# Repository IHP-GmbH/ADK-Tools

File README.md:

# adk-tools

Single Docker image for the heterogeneous integration flow: every tool of the
ecosystem, pre-wired, callable by name. Versions are pinned three ways: the
submodules under `tools/`, the staged sources and engines in `staging.pin`, and
the Nix inputs in `flake.lock`.

## Status

> [!WARNING]
> adk-tools is an alpha. What is checked is the build: `./build.sh` runs its
> verify gate on the image it makes. The flow's results are not: no assembly
> this image exports or checks is qualified, and the path that builds dies
> from RTL has not run end to end (`docs/E2E_BUILD_VARIANT.md`).

## Quickstart

A clone of this repository alone can neither build nor run anything today.
No image is published, to a registry or as a download: you build it locally
(see Build) and run the image you built. Building needs sources that are not
public yet.

### Build

Building needs Docker and Nix on the host, checkouts of the six sibling
repositories `staging.pin` lists at the commits it pins (beside this
repository, or in the directory `STAGE_SIBLINGS` names), and the `die-views/`
folder of an adk-examples checkout (not public yet) whose records match
`die-views.sha256` (`STAGE_DIE_VIEWS_DIR` names that folder). None of the six
pinned commits can be fetched from a public remote yet (`ci/pin-set.json` marks
them `"reachable": "local-only"`). The two `--check` calls below find a missing
piece in seconds; run them first.

`build.sh` compiles the pinned toolchain into one Docker image and copies
OpenROAD, LibreLane, its interpreter, the sg13g2 PDK and the simulation
engines and viewers from the host's Nix store into the image's own store (see
Notes). At the commit you build, realise them once before the build and keep
the result links (they keep the paths from garbage collection). Most come from
the binary cache; vams-devshell and Xschem build locally, and mixsim-iverilog
builds locally and runs Icarus Verilog's regression suite.

```bash
# the clone lives at ADK_TOOLS_ROOT, outside ADK_WORK (see below); the
# die-views/ folder of the adk-examples checkout at ADK_EXAMPLES_ROOT has to
# match die-views.sha256
export ADK_TOOLS_ROOT=~/adk-tools ADK_EXAMPLES_ROOT=~/adk-examples
export STAGE_DIE_VIEWS_DIR="$ADK_EXAMPLES_ROOT/die-views"
git clone --branch vYYYY.MM --recurse-submodules https://github.com/IHP-GmbH/ADK-Tools.git \
    "$ADK_TOOLS_ROOT"
cd "$ADK_TOOLS_ROOT"
./stage-sources.sh --check && ./stage-die-views.sh --check
nix build .#openroad .#librelane .#librelane-python .#sg13g2-pdk \
    .#cosim-devshell .#mixsim-ngspice .#mixsim-iverilog .#sg13g2-osdi \
    .#gtkwave .#gaw .#xschem .#vams-devshell
# ~1 h the first time, cached afterwards; JOBS=N overrides the default 8
# parallel compile jobs
./build.sh

# run.sh takes the image by its ID (sha256:<64 hex>), never a tag, and has no
# default: read the ID of the image you just built once
export ADK_TOOLS_IMAGE="$(docker image inspect --format '{{.Id}}' adk-tools:dev)"
"$ADK_TOOLS_ROOT/run.sh" --examples "$ADK_EXAMPLES_ROOT"
```

The examples' `release-lock.json` names the reference image they were checked
on and the pin set it was built from. Your build has its own ID: `run.sh`
names both IDs in one note line and runs it, and refuses an image whose
`org.ihp.adk-tools.pin-set` label, which `build.sh` writes, is not the lock's
pin set.

### Running it

With `ADK_TOOLS_IMAGE` set:

```bash
# X11 passthrough for the GUIs; ~/adk-work mounted at /work; capped at 8g and
# 4 CPUs, change with ADK_MEM_LIMIT and ADK_CPUS; ADK_NETWORK=none runs it
# with no network
./run.sh                              # interactive shell
./run.sh --examples ~/adk-examples    # the examples, from an adk-examples checkout,
                                      # held to its lock (an image
                                      # without the closure label needs the
                                      # host's Nix store, see Notes)
./run.sh bash < script.sh             # run a script piped in, no terminal needed
```

Inside the shell, `adk-tools` prints this table with the pinned versions of
the running image.

The examples live in their own repository, adk-examples, which is not public
yet. Its `release-lock.json` names the reference image they were checked on
and its pin set, and `run.sh --examples <checkout>` starts an image of that pin
set, with the checkout mounted read-only at `/examples`. Each example's
`README.md` is its page: what to run, and what the run should show.
`examples/two_die_interposer` in this repository is not one of them: it is the
test fixture of the image's own checks.

## Working in the shared folder

`run.sh` mounts a host directory (`~/adk-work`, override with `ADK_WORK=...`) at
`/work` inside the container, so files written on either side are immediately
visible on the other. A relative `ADK_WORK` is taken from the directory you call
`run.sh` from; either way `run.sh` binds it by its absolute path and names it on
its first stderr line, `run.sh: /work is <path>`. What a program calling
`run.sh` can rely on (its notes, exit codes and refusals) is in
[docs/RUN_SH.md](docs/RUN_SH.md).

Keep the adk-tools clone apart from that directory: clone it once to
`ADK_TOOLS_ROOT` (`~/adk-tools` above), outside `ADK_WORK`, leave it at the
version of the image you run (the release tag, or the commit you built), and
call `run.sh` by its path from wherever you work. `run.sh` refuses to start when `ADK_WORK` holds its clone, which the
container would then see and could write, or lies inside it, where a git clean
in the clone would delete your runs.

```bash
export ADK_TOOLS_ROOT=~/adk-tools ADK_WORK=~/adk-work ADK_EXAMPLES_ROOT=~/adk-examples
"$ADK_TOOLS_ROOT/run.sh" --examples "$ADK_EXAMPLES_ROOT"
```

The work directory is the recommended place to keep your designs: edit
with the bundled GUIs/editors in the container, keep the files (and your git
history) on the host. The image writes nothing there unless you ask; two
subdirs are the usual layout:

```
/work/<example>            an example copied in from /examples, as its page says
/work/heterogenic-designs  your persistent designs (survives image rebuilds)
```

The runtime image carries no examples. Start it with an adk-examples checkout
(`run.sh --examples`); inside the container, `adk-example` prints that line.

Scaffold a new design instead of starting from a blank dir:

```bash
adk-new-project my_design          # -> /work/heterogenic-designs/my_design
```

It lays out the same structure as the bundled example, a clean split between
source and generated artifacts:

```
my_design/
  kicad/       KiCad source you author (schematic, PCB, .pretty, fp-lib-table)
  chiplets/    die GDS inputs (+ pin lists) for the gds-to-kicad prior steps
  outputs/     export products: <board>.chiplet + MANIFEST.md at the root; the
               GDS layouts + DRC sidecars under outputs/layout/; the DRC
               reports under outputs/reports/
```

Author the board under `kicad/`, run the Chiplet Export plugin in pcbnew with
its output directory set to the sibling `outputs/`, then open the result with
`chiplet-studio outputs/<board>.chiplet`. The scaffolded `.gitignore` already
keeps the heavy/scratch files (the full `_complete.gds`, the intermediate
`.hyp`, the DRC working dir, logs and KiCad caches) out of git while tracking
the light deliverables, so `git init` in the project is ready to use.

## Tools

| Command          | Tool                                  | Kind |
|------------------|---------------------------------------|------|
| `kicad`          | KiCad fork (+ `pcbnew`, `kicad-cli`, chiplet export plugin preloaded) | GUI |
| `chiplet-studio` | 3D assembly viewer / `.chiplet` editor | GUI |
| `gds-to-kicad`   | GDS -> KiCad symbol + footprint generator (unified GUI) | GUI |
| `hyp-to-gds`     | HyperLynx -> GDS converter             | CLI |
| `adk-drc`        | ADK assembly DRC runner                | CLI |
| `klayout`        | KLayout (version pinned by the studio submodule) | GUI/CLI |
| `adk-smoke`      | Board export + dual DRC, asserts green  | CLI |

Data roots baked in (and exported as env), named after their IHP
repositories: `INTERPOSER_PDK_ROOT=/opt/adk-tools/OpenIntM4TM2`,
`INTERCONNECT_PDK_ROOT=/opt/adk-tools/IHP-Interconnect-IntM4TM2`,
`PDK_ROOT=/opt/adk-tools/IHP-Open-PDK` (SG13G2 KLayout slice: the
SG13_dev PCell library + tech, pinned in the Dockerfile, so
`hyp-to-gds` builds vias from real `via_stack` PCells, not the
rectangle fallback), plus `ADK_ROOT` and `GDS_TO_KICAD_ROOT`. The
two-die interposer test fixture lives in this repo under `examples/` (not in the
runtime image; the verify build puts it at `/opt/adk-tools/examples`,
regenerates it and DRC-gates it); it follows the same `kicad/` + `chiplets/` + `outputs/` template
as a scaffolded project. Python worker venv: `/opt/adk-tools/venv`
(`KICAD_CHIPLET_PYTHON` already points at it).

Dies on an IntM4TM2 interposer mount on the plane the interposer PDK states,
`beol.attachment_surface_z_um` in `libs.tech/intm4tm2_stack.json`.
`ci/check_attach_plane.py` holds every IntM4TM2 `.chiplet` in the plugin, in
Studio and in `examples/` to it, and the consumers' copies of the PDK's stack
files to the PDK; it runs in CI and in every verify build, and its docstring
states exactly which files it walks.
`ci/check_kicad_templates.py` does the same for the staged interposer-pnr and
packaging-flow copies of the PDK's KiCad rule templates, in every verify build.

`openroad/` holds a host-side sidecar that lints an assembly with OpenROAD's
`read_3dbx` / `check_3dblox`, using a separately pinned OpenROAD image. It is
not part of the distribution image; see `openroad/README.md`, which also
states plainly what that linter does and does not catch.

The interposer KLayout technology is pre-registered (`KLAYOUT_PATH`
includes the OpenIntM4TM2 tree), so exported interposer/assembly GDS
files open with named, colored layers: `klayout -n intm4tm2 <file>.gds`,
or pick `intm4tm2` in the technology selector.

The PDK's `IntM4TM2 Interposer > Verification` menu (`Interposer DRC…`,
`Interposer LVS…`) needs a KLayout with Qt bindings, and the image's KLayout
is built without them: the entries are listed, and choosing one reports
`AttributeError: module 'pya' has no attribute 'QDialog'`. KLayout itself
starts normally, and the PDK's other menu entries do not use Qt bindings. The
runners behind that menu are
unaffected; call them directly from `libs.tech/klayout/tech/drc/run_drc.py`
and `libs.tech/klayout/tech/lvs/run_lvs.py` under `$INTERPOSER_PDK_ROOT`.

## Updating an existing clone

This section and the two after it are for building (Quickstart, Build). To run
a newer release, check out its tag and build it.

```bash
# the Quickstart's exports, again in a fresh shell
export ADK_TOOLS_ROOT=~/adk-tools ADK_EXAMPLES_ROOT=~/adk-examples
export STAGE_DIE_VIEWS_DIR="$ADK_EXAMPLES_ROOT/die-views"
cd "$ADK_TOOLS_ROOT"
git fetch --tags
git checkout vYYYY.MM    # a release clone sits on a tag, so there is nothing to pull
git submodule update --init --recursive
./stage-sources.sh --check && ./stage-die-views.sh --check
./build.sh    # cached stages rebuild only what changed
```

The sibling checkouts have to hold the new pins (a `git fetch` in each), and
the adk-examples checkout has to hold die-views records that match the new
`die-views.sha256` (update it until they do); the two `--check` calls say
which one does not.

One-time cleanups, depending on how old the clone is:

- Clones from before the demo moved into `examples/` still carry the
  removed `kicad_designs` submodule as leftovers:
  `rm -rf tools/kicad_designs .git/modules/tools/kicad_designs`
- If the default job count changed since your last build (it keys the
  compile layers), the heavy stages rebuild once (~40 min), then cache
  normally again.
- A `/work/example` from an older image stays as it is. It was the demo copied
  from this clone; the examples now come from adk-examples.

## Branch model

`main` is frozen per release and pins each tool's `main`. `dev` is where the
suite is integrated and tested, and pins each tool's `dev` branch instead, so
`git submodule update --remote` follows the right side on each branch. Tools
without ongoing work keep `branch = main` in `.gitmodules` on both sides until
they need a `dev`; check that file for which is which.

Feature work happens on a branch of the tool's `dev`, and is evaluated by
checking it out in the submodule and rebuilding (see below). A release folds
each tool's `dev` into its `main`, then re-pins adk-tools `main`.

## Updating / testing a tool release

```bash
# bump one tool to its latest upstream branch (dev on this branch, main on main)
git submodule update --remote tools/adk
git add tools/adk
python3 -B ci/pin_set.py    # the pin set records every staged gitlink
git commit -am "Bump adk to <ref>"
./build.sh

# try an arbitrary branch of one tool against the rest of the pinned stack
cd tools/chiplet-studio && git fetch && git checkout feature/x && cd ../..
./build.sh
```

The pin set takes each tool's commit from the gitlink git has staged, not from
the submodule's checkout, so stage the bump before you regenerate it. The
image is labelled with the committed pin set: `build.sh` refuses a
`ci/pin-set.json` that differs from the commit or from what the staged pins
give, so commit the regenerated file before you build. In the second case
nothing is staged: the image carries `feature/x` while its
`org.ihp.adk-tools.pin-set` label still names the pinned commit, so do not run
such an image under an examples checkout's `release-lock.json`.

`build.sh` always builds the `verify` stage first: it regenerates the
two-die interposer demo headless through the full pipeline (pcbnew -> writers ->
hyp_to_gds -> assembly DRC), runs the Chiplet Studio test suite and the
plugin test suite inside the image. A broken combination does not produce a
tagged image. `--skip-verify` exists for quick iteration only.

To develop a Python tool against the pinned stack, mount your checkout over
the baked-in copy:

```bash
docker run --rm -it -v "$PWD/chiplet_kicad_plugin":/opt/adk-tools/chiplet_kicad_plugin ... adk-tools:dev
```

## Notes

- The image's Magic is 8.3.610, from LibreLane's Nix closure, and the PDK's Magic
  techfiles require 8.3.617 (ihp-sg13g2) and 8.3.657 (ihp-sg13cmos5l), so a LibreLane
  Classic flow run in the image fails at `Magic.StreamOut`. Build dies with
  chiplet-flow's Chiplet flow (`meta.flow: Chiplet`), which runs no Magic step.
- The image carries OpenROAD, LibreLane, its interpreter, the sg13g2 PDK and
  the LibreLane launcher in its own `/nix/store`: the closure
  `nix/host-closure.txt` lists, each path pinned with its narHash in
  `nix/host-closure.lock`. `build.sh` refuses to pack unless every path is in
  the build host's store with that narHash, and the verify stage recomputes
  each one in the image. The image sets `OPENROAD`, `ADK_NIX_LIBRELANE`,
  `ADK_NIX_LIBRELANE_PYTHON`, `ADK_NIX_SG13G2_PDK` and the launcher pair in its
  ENV, and carries the `org.ihp.adk-tools.nix-closure-inside` label (the lock's
  sha256). For such an image `run.sh` mounts nothing of the host's store, passes
  none of those variables, ignores `ADK_OPENROAD` with a note, and needs no Nix
  on the host. It refuses an image whose label is there but is not a sha256.
- An image without that label needs the host's
  Nix store: `run.sh` takes, read-only, the OpenROAD the image's
  `org.ihp.adk-tools.nix-openroad` label names (staging.pin's
  `NIX_OPENROAD_OUTPATH`), or `ADK_OPENROAD` when set, and sets `OPENROAD` to
  it. It refuses to start when the host has no Nix store or that path is not in
  it, with a line starting `needs Nix on the host:`; realise it with
  `nix build .#openroad`. An image without the `nix-openroad` label needs
  `ADK_OPENROAD`.
- What goes in from the host's store, for such an image, is the closure of OpenROAD, LibreLane,
  its interpreter and the sg13g2 PDK, listed in `nix/host-closure.txt`.
  `build.sh` refuses unless that file is the store's closure of the four, and
  writes it on the image as the `org.ihp.adk-tools.nix-host-closure` label (the
  paths joined by single spaces) with its sha256 in
  `org.ihp.adk-tools.nix-host-closure-sha256`. `run.sh` checks the list against
  its sha256 and binds each listed path on its own, read-only, at its own path,
  so the image's own `/nix/store` stays visible beside them; a listed path the
  host lacks is not bound and is counted in a note. No launch calls Nix. An
  image without the two labels, or an `ADK_OPENROAD` the list does not name,
  gets the whole host store instead, which hides the image's own store paths.
  A die run recorded under another sg13g2-pdk path names a PDK outside the
  list; rebuild that die under this image's PDK.
- Such an image ships no LibreLane, no LibreLane interpreter and no sg13g2 PDK
  either; a page that builds a die in the container takes them from the same
  store. `run.sh` passes the paths the image's `org.ihp.adk-tools.nix-librelane`,
  `org.ihp.adk-tools.nix-librelane-python` and `org.ihp.adk-tools.nix-sg13g2-pdk`
  labels name (staging.pin's `NIX_LIBRELANE_OUTPATH`, the `bin/python3.<minor>`
  of `NIX_LIBRELANE_PYTHON_OUTPATH`, and `NIX_SG13G2_PDK_OUTPATH`) as
  `ADK_NIX_LIBRELANE`, `ADK_NIX_LIBRELANE_PYTHON` and `ADK_NIX_SG13G2_PDK`, the
  names the Nix build shell sets, when they are on the host and in the list
  bound. When one is not, it says so and starts anyway, and that page refuses;
  realise them with
  `nix build .#librelane .#librelane-python .#sg13g2-pdk`.
- The image does carry the co-simulation engine chiplet-cosim runs: Icarus and
  a python3.13 with cocotb 2.0.0 in its own site-packages, at the Nix store
  paths staging.pin's `NIX_COSIM_*` lines name, under the image's `/nix/store`.
  `COSIM_DEVSHELL` links to the flake's `cosim-devshell`, a store path whose
  `bin/` holds only `python3`, `iverilog` and `vvp`, linked into them; none is
  on `PATH`. Only when `run.sh` mounts the whole host store (see above) does
  that hide the image's; then the engine comes from the host's store, and
  `run.sh` says when it is not there; realise it with
  `nix build .#cosim-devshell`.
- It carries a mixed-signal engine the same way: ngspice 45, an Icarus with
  libvvp, and the six sg13g2 OSDI models compiled for generic x86-64, at the
  paths staging.pin's `NIX_MIXSIM_*` and `NIX_SG13G2_OSDI_OUTPATH` lines name.
  `MIXSIM_DEVSHELL` holds `bin/ngspice`, `bin/iverilog`, `bin/vvp`,
  `lib/libvvp.so`, `lib/ngspice` (with the ivlng shim d_cosim loads) and
  `osdi/`; none is on `PATH`. Give d_cosim `lib/libvvp.so` and
  `lib/ngspice/ivlng` by absolute path, and load the models with `pre_osdi`.
  Under a whole-store mount, realise it with
  `nix build .#mixsim-ngspice .#mixsim-iverilog .#sg13g2-osdi`.
- For a gf180mcuD die in a mixed case it carries that PDK's `design.ngspice`
  and `sm141064.ngspice` and no cell library, at the GF180 layer sheet's
  commit. `COSIM_GF180_ROOT` points at them, and it is the only place
  chiplet-cosim reads a gf180mcuD models entry's root from.
- For a transistor-level ihp-sg13g2 die it carries, under
  `$PDK_ROOT/ihp-sg13g2`, every ngspice model file the MOS, diode, resistor
  and capacitor corner libraries include, in any section and at any depth, and
  the stdcell spice (`sg13g2-models.sha256` lists them, and
  `ci/check_sg13g2_models.py` recomputes that list), at the slice's commit, and
  copies of the OSDI files `psp103`, `psp103_nqs`, `r3_cmc` and `mosvar` in
  `libs.tech/ngspice/osdi`. A link would not do there: chiplet-cosim refuses
  an OSDI file that resolves outside the PDK.
- It carries two waveform viewers and a schematic editor the same way, and
  these are on `PATH`: `gtkwave` (GTKWave 3.3.121, for VCD and FST), `gaw`
  (GAW, for ngspice's raw files, binary or ASCII) and `xschem` (Xschem
  3.4.8RC, upstream commit 8d2088e, with its device symbols under
  `XSCHEM_SHAREDIR`), at the paths staging.pin's `NIX_GTKWAVE_OUTPATH`,
  `NIX_GAW_OUTPATH` and `NIX_XSCHEM_OUTPATH` name. All three need a display
  (`ADK_DISPLAY`); `xschem -x -q -n -s` netlists without one. Under a
  whole-store mount, realise them with `nix build .#gtkwave .#gaw .#xschem`.
- It carries a Verilog-AMS engine the same way: gnucap and its Verilog-AMS
  model compiler in one prefix, at the paths staging.pin's
  `NIX_VAMS_GNUCAP_OUTPATH` and `NIX_VAMS_DEVSHELL_OUTPATH` name.
  `VAMS_DEVSHELL` holds `bin/gnucap`, `bin/gnucap-conf`, `bin/gnucap-mg-vams`,
  `bin/gnucap-modelgen`, `bin/g++` and `bin/c++`; none is on `PATH`. Compile a
  model with `gnucap-mg-vams` and that `g++` (flags from
  `gnucap-conf --cppflags`), then `load` the `.so` in gnucap. Under a
  whole-store mount, realise it with `nix build .#vams-devshell`; it is not
  in the binary cache, so that builds it.
- It carries the EDA views of the two built bondpad dies, their gate-level
  netlists and CDL among them, under `ADK_DIE_VIEWS`
  (`/opt/adk-tools/die-views`), one directory per die named by the layout
  sha256 its contract binds. A die with no directory there has no
  views. Copy a record out before using it; the image's copy is the reference.
  `die-views.sha256` pins every byte, and `staging.pin` pins that listing as
  `STAGE_DIE_VIEWS_SHA256`. Building the image needs the records:
  set `STAGE_DIE_VIEWS_DIR` to the directory holding their `records/`.
- GUIs need an X server. `run.sh` takes the display from `ADK_DISPLAY` (`:N`,
  or `none`), else a local `DISPLAY`, else the newest ThinLinc session whose
  socket is yours, and passes its cookie from `XAUTHORITY`, the ThinLinc
  session or `~/.Xauthority`, whichever holds one for that display. It prints
  the display it chose. The image itself forces Mesa's
  software path (`LIBGL_ALWAYS_SOFTWARE=1`, `GALLIUM_DRIVER=llvmpipe`, set in
  the Dockerfile) so the GUIs stay stable over remote X without a GPU;
  otherwise KiCad's GL canvas crashes when the host can't provide a DRI3
  device. Pass a real GPU and `-e LIBGL_ALWAYS_SOFTWARE=0` for hardware
  acceleration.
- The image bundles GPL-licensed tools: the pinned submodules under `tools/`,
  public in the IHP-GmbH org; the staged trees `staging.pin` pins, not public
  yet, whose source the image carries as git checkouts under
  `/opt/adk-tools/staging/<tree>`; and programs from the Nix closures copied
  into the image (Icarus Verilog, GTKWave, GAW, Xschem, gnucap and
  modelgen-verilog, nix-eda's KLayout, and the OpenSTA inside OpenROAD), whose
  source is at the revisions `flake.lock` and `flake.nix` pin. `NOTICE.md`
  lists them all.
- KiCad ships the official v9 symbol/footprint libraries (pinned tag,
  `KICAD_LIBS_TAG` build arg). 3D model packages are not included.
- Text editors are bundled for in-container edits to files under `/work`:
  `vim` (terminal) and `featherpad` (a light Qt GUI editor; needs X, like the
  other GUIs).

## License & notices

This repository is **GPL-3.0-or-later** (`LICENSE`), with one rule on top: a
file's own `SPDX-License-Identifier` line decides its license. The record format
schemas in [`formats/`](formats/) and the files of ours whose SPDX line says
Apache-2.0 (most of `ci/`, `nix/`, `nix-tail/`, their tests and `flake.nix`) are
**Apache-2.0**; its text is in
[`formats/LICENSE`](formats/LICENSE). A file with no SPDX line is under `LICENSE`,
and the third-party files `NOTICE.md` lists keep their own license.
The image is a **mere aggregation** of independently licensed tools; each keeps its
own license, and the bundled set spans GPL, Apache-2.0, CC-BY-SA-4.0 and permissive
(MIT/BSD) licenses. See
[`NOTICE.md`](NOTICE.md) for the per-component licenses, source URLs, and the GPL
corresponding-source obligation that applies when you redistribute the image.

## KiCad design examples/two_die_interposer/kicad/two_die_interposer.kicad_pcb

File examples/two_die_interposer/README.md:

# two_die_interposer

This folder is the test fixture of the image's own checks (the gds2kicad prior
steps, the writers, adk-smoke, carrier DRC, the reproducibility check). It is
not an example for users: those live in the adk-examples repository, and
`run.sh --examples` mounts them.

Reference heterogeneous-design project for the adk-tools flow: two dies mounted
on an IntM4TM2 interposer, connected through cu-pillar / micro-bump interconnect
(2.5D), with wire-bond I/O pads at the interposer edge. It doubles as the
template that `adk-new-project` scaffolds, so its layout is the recommended one
for any new design.

## Layout

```
two_die_interposer/
  kicad/       KiCad source (the human-authored input)
    two_die_interposer.kicad_pro / .kicad_sch / .kicad_pcb
    two_die_interposer.kicad_sym    (project symbols, produced by gds2kicad)
    two_die_interposer.pretty/      (project footprints, produced by gds2kicad)
    sym-lib-table / fp-lib-table    (register those two libraries with the project)
  chiplets/    gds2kicad prior-steps inputs (see chiplets/README.md)
    Metal_Test.gds                 die layout shared by both dies
    metal_test_chiplet.pins.json   curated 58-pad pin list
  outputs/     export products written by the Chiplet Export plugin
    two_die_interposer.chiplet            chiplet-studio entry point
    MANIFEST.md                           index of the products
    layout/    GDS layouts + their sidecars
      two_die_interposer_interposer.gds   referenced by the .chiplet
      *.boundaries.json / *.ixn_methods.json  assembly-DRC sidecars
    reports/   DRC reports: *_assembly_drc.lyrdb, *_cupillar_drc.json
    (regenerated, git-ignored: layout/_complete.gds, .hyp, reports/assembly_drc/, logs/)
```

The `.chiplet` references its interposer GDS by a `layout/<file>` relative path,
which chiplet-studio resolves against the `.chiplet`'s own directory; it then
auto-detects the `_complete.gds` from that same `layout/` dir, and the assembly
DRC finds each `*.boundaries.json` next to its GDS. So the GDS layouts and their
sidecars travel together under `layout/`, the DRC reports under `reports/`, and
only the `.chiplet` + `MANIFEST.md` sit at the `outputs/` root. Each die's own
layout is `chiplets/Metal_Test.gds`, shipped with the example: the footprint (and
the `.chiplet` it produces) reference it board-relative as
`../chiplets/Metal_Test.gds`, so the export and chiplet-studio resolve the die
layout from the example itself, not from any external tool tree. This is the same
die that seeds the reproducible prior steps below.

## Prior steps: chiplet footprints and symbols (gds2kicad)

The KiCad library this board is built on (`kicad/two_die_interposer.pretty/*` and
`kicad/two_die_interposer.kicad_sym`) is produced from the chiplet layouts with
the gds2kicad tools, before any board work starts. Those inputs and the exact
recipe live in `chiplets/` (see `chiplets/README.md`). The verify build reruns
the reproducible steps and gates them: the die symbol and the I/O pad are
regenerated and diffed against the committed library, the pin list is checked
against the committed footprint, and the footprint converter is run on
`Metal_Test.gds` as a liveness check.

## Open it

The runtime image does not carry this project. Copy it on the host from the
adk-tools clone you run `run.sh` from, into the folder mounted at `/work`
(`/work/example` is the disposable spot; for persistent work use your own area):

```bash
cp -r "$ADK_TOOLS_ROOT/examples/two_die_interposer" "$ADK_WORK/example"
mkdir -p "$ADK_WORK/heterogenic-designs"
cp -r "$ADK_TOOLS_ROOT/examples/two_die_interposer" "$ADK_WORK/heterogenic-designs/"
```

Then open the copy:

```bash
chiplet-studio /work/example/outputs/two_die_interposer.chiplet
kicad          /work/example/kicad/two_die_interposer.kicad_pro
gds-to-kicad   # unified symbol + footprint GUI; load chiplets/Metal_Test.gds to reproduce the die library
```

## Regenerate (outputs)

The verify build regenerates `outputs/` from `kicad/` on every image build and
gates it through the assembly DRC. To do it by hand:

```bash
python3 /opt/adk-tools/chiplet_kicad_plugin/plugins/chiplet_export/tests/regenerate_wirebond_demo.py \
    --require-drc \
    --board   example/kicad/two_die_interposer.kicad_pcb \
    --output-dir example/outputs
```

`adk-smoke` runs the same export end-to-end into a throwaway dir.

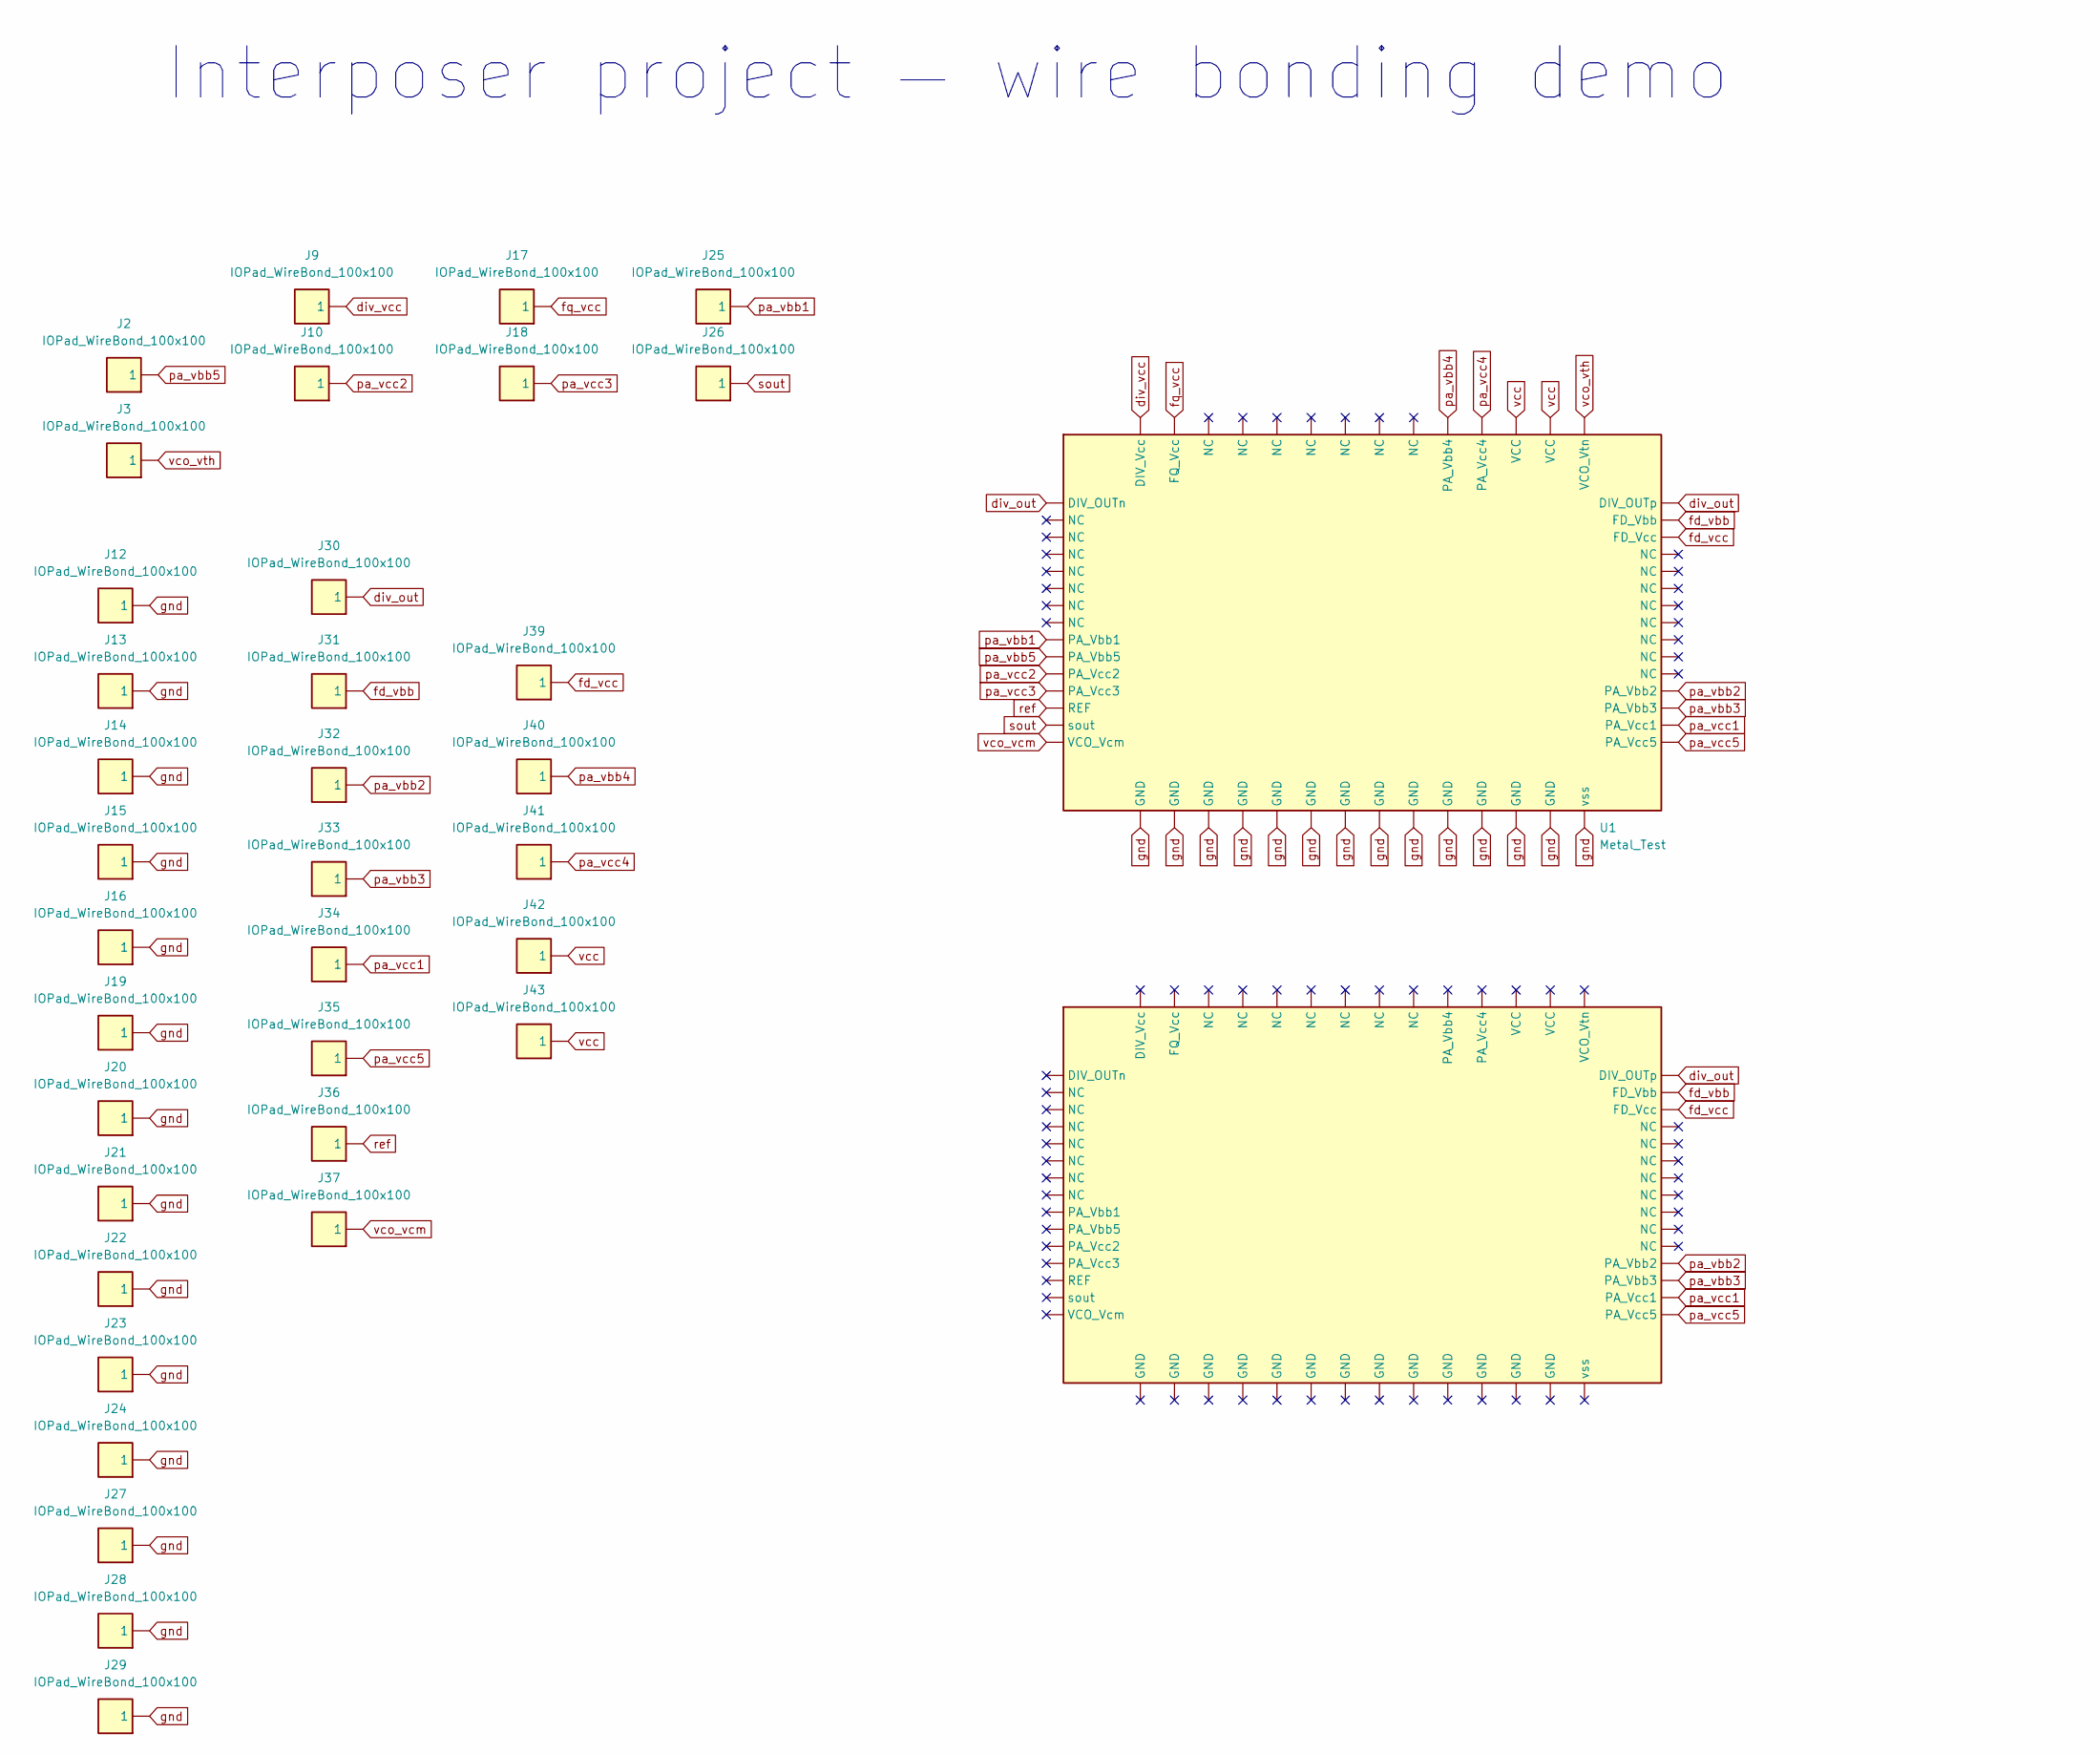
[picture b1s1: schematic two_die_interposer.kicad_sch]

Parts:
J2, J3, J9, J10, J12, J13, J14, J15, J16, J17, J18, J19, J20, J21, J22, J23, J24, J25, J26, J27, J28, J29, J30, J31, J32, J33, J34, J35, J36, J37, J39, J40, J41, J42, J43: IOPad_WireBond_100x100; interposer_bondpad
U1, U2: Metal_Test; metal_test_chiplet

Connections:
div_out: J30.1 (1_1), U1.DIV_OUTn, U1.DIV_OUTp, U2.DIV_OUTp
div_vcc: J9.1 (1_1), U1.DIV_Vcc
fd_vbb: J31.1 (1_1), U1.FD_Vbb, U2.FD_Vbb
fd_vcc: J39.1 (1_1), U1.FD_Vcc, U2.FD_Vcc
fq_vcc: J17.1 (1_1), U1.FQ_Vcc
gnd: J12.1 (1_1), J13.1 (1_1), J14.1 (1_1), J15.1 (1_1), J16.1 (1_1), J19.1 (1_1), J20.1 (1_1), J21.1 (1_1), J22.1 (1_1), J23.1 (1_1), J24.1 (1_1), J27.1 (1_1), J28.1 (1_1), J29.1 (1_1), U1.GND, U1.vss
pa_vbb1: J25.1 (1_1), U1.PA_Vbb1
pa_vbb2: J32.1 (1_1), U1.PA_Vbb2, U2.PA_Vbb2
pa_vbb3: J33.1 (1_1), U1.PA_Vbb3, U2.PA_Vbb3
pa_vbb4: J40.1 (1_1), U1.PA_Vbb4
pa_vbb5: J2.1 (1_1), U1.PA_Vbb5
pa_vcc1: J34.1 (1_1), U1.PA_Vcc1, U2.PA_Vcc1
pa_vcc2: J10.1 (1_1), U1.PA_Vcc2
pa_vcc3: J18.1 (1_1), U1.PA_Vcc3
pa_vcc4: J41.1 (1_1), U1.PA_Vcc4
pa_vcc5: J35.1 (1_1), U1.PA_Vcc5, U2.PA_Vcc5
ref: J36.1 (1_1), U1.REF
sout: J26.1 (1_1), U1.sout
vcc: J42.1 (1_1), J43.1 (1_1), U1.VCC
vco_vcm: J37.1 (1_1), U1.VCO_Vcm
vco_vth: J3.1 (1_1), U1.VCO_Vtn

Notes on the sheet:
Interposer project — wire bonding demo

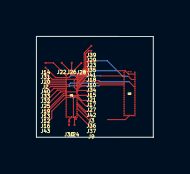
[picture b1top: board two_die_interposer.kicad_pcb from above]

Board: 4 copper layers, 6.5 x 5.6 mm, 37 parts (0 on the bottom side), 21 nets.

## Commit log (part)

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2026-06-05 Initial skeleton: 8 pinned submodules, multi-stage Dockerfile, wrappers, build/run scripts
2026-06-05 README + make klayout libs resolvable for build-time gtest discovery
2026-06-05 Rename shared work dir to heterogenic-designs
2026-06-05 README: point clone at IHP-GmbH/ADK-Tools
2026-06-05 Cap heavy-stage compile jobs via JOBS arg (default 16)
2026-06-05 Bump plugin: discovery walk accepts IHP repo dir names
2026-06-05 Self-contained demo + UX fixes from first manual test
    - bump gds_to_kicad (Metal_Test.gds now tracked) and kicad_designs (U2
    GDS_FILE uses the variable form): studio renders die geometry from a
    clean image instead of fallback boxes
    - ship studio's build/python module dir (ScriptEngine PYTHON_MODULE_DIR)
    - run.sh: named container user via generated passwd/group; TTY flags only
    when stdin is a terminal
2026-06-05 Exclude backup/* tags from manifest describe
2026-06-05 Bump plugin: repo-name aliases in all walkers
2026-06-05 Manifest lookup by .gitmodules section, not path (git mv divergence)
2026-06-05 Bump OpenIntM4TM2: repo-name aliases in bump_mirror walks
2026-06-05 Folder structure round: IHP repo names for PDKs, stable /work layout
    - tools/interposer -> tools/OpenIntM4TM2, tools/interconnect_pdk ->
    tools/IHP-Interconnect-IntM4TM2 (match the IHP repository names; env
    roots updated, discovery is env-first so the walk names don't matter
    in-image)
    - ecosystem ENVs moved from deps to runtime: env changes no longer
    invalidate the builder caches
2026-06-05 KiCad standard libraries + portable self-contained example
    - kicad-libs stage: official v9 symbol/footprint libraries (pinned tag
    9.0.9.1; the 9.99 fork predates .kicad_symdir so v9 is the compatible
    set), installed with their default global tables; entrypoint pre-seeds
    the user tables so no first-run dialog.
    - Bump plugin (CONNECTION write-back styled, relative layout refs) and
    kicad_designs (demo regenerated: portable .chiplet, scrubbed texts,
2026-06-05 release.sh: push to ghcr + prune untagged versions
    Single-digest storage policy: tags are free pointers, superseded
    untagged digests are deleted (small private-package quota on the org
    plan).
2026-06-05 Default to 8 build jobs; document git+build.sh as primary channel
    Registry stays best-effort (small private-package quota on the org
    plan).
2026-06-05 Bump plugin: fixture discovery covers examples/ layout
2026-06-05 README: updating-an-existing-clone procedure
2026-06-07 Bake SG13G2 PCell slice; bump plugin for PCell vias + JSON fallback
    New sg13g2-pdk stage: 1.8MB slice of IHP-Open-PDK (sg13g2_pycell_lib,
    pycell4klayout-api and pypreprocessor at pinned refs, tech files,
    Apache-2.0 LICENSE) baked at /opt/adk-tools/IHP-Open-PDK with
    PDK_ROOT set. python3-tk installed in the runtime stage (a deps change
    would re-key the builder caches), psutil added to the worker venv:
    both are runtime deps of the PCell library.
2026-06-09 Bump kicad submodule to the autosave use-after-free fix
    Points tools/kicad at KiCad-ADK-MOD 4732d28, which keys the LOCAL_HISTORY
    autosave savers by stable addresses so a frame's saver is always unregistered
    on destruction. Fixes the segfault seen when editing a symbol shape after
    switching projects (autosave invoked a lambda capturing a freed frame).
2026-06-10 Run adk, gds_to_kicad and interposer suites in the verify gate
    Three new fail-fast pytest RUNs ahead of the demo regen close the gap
    where these suites only ever ran on the host. The worker venv gains
    jinja2 (the adk DRU generator imports it).
    Bump the five tool pins to the integration-audit batch: discovery
    aliases plus strict format_version (chiplet-studio), interconnect id
    validation, layer guard and CI (plugin), boundary manifest validation
2026-06-10 Bump plugin: pre-filled interposer LYP picker in the export dialog
    Verify gate green: adk 48, gds_to_kicad 171/20 skipped, interposer 34,
    studio ctest 562/562, plugin 164/2 skipped, adk-smoke PASS.
2026-06-10 Bump OpenIntM4TM2: filler macro menu under IntM4TM2, not SG13G2
2026-06-11 Bump gds_to_kicad: write outputs to the working dir, not the install dir
    Picks up the non-root fix (574d0b1) so the GDS->KiCad converters resolve a
    writable base (CWD / $GDS_TO_KICAD_DATA_DIR) instead of the read-only
    /opt/adk-tools install dir, which crashed the footprint GUI at startup under
    run.sh. Image must be rebuilt from git to take effect; ghcr unchanged.
2026-06-18 Bump chiplet-studio: docker PDK env + remove Clip cross-section
    Submodule c72cec5 -> ef00330:
    - Docker image bakes INTERCONNECT_PDK_ROOT / INTERPOSER_PDK_ROOT / PDK_ROOT at
    fixed container paths, which fixes CuPillar/bump body rendering in the
    wire-bond demo (the fragment lookup reads the env var first).
    - Remove the cross-section Clip toolbar and engine; move the shape Filter to
    the top-right corner.
2026-06-18 Document mixed-license aggregate in NOTICE.md (#1)
    The image bundles GPL, Apache-2.0 and CC-BY-SA-4.0 components. Add NOTICE.md
    listing each component's license + source URL and the GPL corresponding-source
    obligation on redistribution; link it from the README.
2026-06-18 Move gds_to_kicad submodule to official IHP-GmbH/gds2kicad
    Repoint tools/gds_to_kicad from the personal Mauricio-xx/gds-to-kicad
    repo to the official IHP-GmbH/gds2kicad (branch main), and bump the pin
    574d0b1 -> 8b95b44 (the GPL-3.0 LICENSE + SPDX-headers commit).
2026-06-18 adk submodule: bump to documentation rewrite (c266a32)
    Docs-only update of the ADK; no build or CI impact (the Dockerfile COPYs
    the working tree, not the pinned commit).
2026-06-18 chiplet_kicad_plugin submodule: bump to docs rewrite (04c3b57)
    Docs-only update (README + tests/README aligned with current code); no
    build or CI impact.
2026-06-18 docs: correct umbrella README and NOTICE against the current build
    - NOTICE: point gds-to-kicad at IHP-GmbH/gds2kicad (the old Mauricio-xx
    repo is archived) and note the move; keeps the GPL corresponding-source
    pointer unambiguous.
    - README: attribute the software-GL (llvmpipe) forcing to the Dockerfile
    ENV, not run.sh.
    - build.sh: fix the JOBS default in the usage comment (8, not 16).
2026-06-18 OpenIntM4TM2 submodule: bump to docs rewrite (8589eb7)
    Docs-only update (PDK README + libs.tech/{klayout,kicad}/README aligned
    with current contents); no build or CI impact.
2026-06-19 chiplet-studio submodule: bump to coord_frame_contract pointer merge (f6c5a7c)
2026-06-19 kicad submodule: bump to NANOMETER_MODIFICATIONS docs fix (c4954f4710)
    Docs-only update of the fork's modification record; no fork source or
    build change.
2026-06-20 Bump chiplet-studio: Phase 1 code-audit corrections (ctest 549 green)
2026-06-20 chiplet_kicad_plugin: bump pin for the phase 3 code audit
    41 audit findings fixed across 8 themed commits plus adversarial-review
    fixes (04c3b573 -> 22e8105): byte-exact writer parity restored against the
    C++ exporters, worker exit-code and flip-chip correctness, runner pipe-
    deadlock fix, dialog close-during-run safety, input robustness and SPDX
    hygiene. Plugin pytest and the wire-bond regen assembly DRC stay green.
2026-06-20 Bump gds_to_kicad pin to the Phase 4 code-audit tip (c0f0029)
    Phase 4 of the code-quality audit landed in gds2kicad: 51 findings fixed
    across 13 commits (output-string escaping, atomic UTF-8 writes, CLI
    robustness/clean errors, pin-pad identity, coordinate/geometry fixes, GUI
    state, dead-code + theme consolidation, doc alignment, new tests). Gate
    178 pass / 20 skip; cross-tool contracts (boundary manifest schema,
    generic.lyp <-> chiplet_pads.json, .kicad_mod/.kicad_sym/.chiplet/CSV
2026-06-21 Bump kicad and chiplet_kicad_plugin pins: Phase 5 code audit
    kicad c4954f4710 -> c95664ec: export_chiplet/export_hyperlynx now escape
    YAML and .hyp scalars and validate IO_CLASS, the headless writer is atomic
    and reports without modal dialogs, plus nanometer rendering, AppImage
    packaging, and NANOMETER_MODIFICATIONS doc fixes.
    chiplet_kicad_plugin 22e8105 -> e7d989e: the byte-locked Python writers
    mirror the same escaping and validation, with new escaper unit tests and
2026-06-21 Harden the umbrella scripts
    run.sh: use a private mktemp dir (0700) with an EXIT-trap cleanup instead of a predictable /tmp/...-<uid> path a co-located user could pre-create. release.sh: trap the ghcr logout so the token is dro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
2026-06-21 Pin worker-venv deps and ship the license texts in the image
    Exact-pin all seven venv pip packages (was only klayout), so one umbrella commit reproduces the same behaviour-defining set instead of re-resolving against live PyPI on a cache-cold rebuild. Copy LIC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
2026-06-21 Add vim and featherpad editors to the runtime image
    Bundled in the runtime-only apt layer (not deps, so the heavy builder
    caches survive) for editing files under the shared /work area without a
    second host terminal.
2026-06-21 Bump chiplet_kicad_plugin and chiplet-studio: export run logging + de-stale
    Plugin (5c487c8): per-run export log file under outputs/logs/, default output dir under a kicad/ project, demo refs aligned to the kicad/ + outputs/ layout.
    chiplet-studio (2316dd2): drop stale kicad_designs/ references for the umbrella examples/ layout (launchers, fixture resolvers, removed the dead RealWorldChipletDemo test).
2026-06-22 Bump kicad: default PCB units to micrometres
    tools/kicad c95664ec -> dc6c7a5e: pcbnew and footprint editor now default
    system.units to micrometres for the chiplet/interposer flow.
2026-06-22 Seed empty global KiCad library tables to fix the startup stall
    KiCad re-enumerated all 155 footprint and 223 symbol libraries (~15k
    footprints) on every launch, freezing on 'loading libraries' because
    HOME=/tmp keeps no fp-info-cache between runs. The chiplet flow resolves
    footprints and symbols from each project's own ${KIPRJMOD} libraries, so the
    seeded global tables are now empty. The full libraries stay on disk under
    /usr/share/kicad and can be re-added from Manage Symbol/Footprint Libraries.
2026-06-22 Restructure demo outputs/: reports/ subdir + MANIFEST; version-stamp the seed
    Bump the plugin pin to the reports/ + MANIFEST change. The demo's DRC reports
    move into outputs/reports/ and a generated MANIFEST.md indexes the products;
    the GDS cluster and the .chiplet stay flat (resolved by sibling lookup). Keep
    .gitignore, .dockerignore and the adk-new-project scaffold in lockstep (the DRC
    scratch is now reports/assembly_drc/).
    adk-entrypoint refreshes /work/example when a newer image ships a changed demo:
2026-06-23 Restructure demo outputs/: layout/ subdir for GDS + sidecars
    Move the wire-bond demo GDS and its JSON sidecars into outputs/layout/, keeping
    the .chiplet and MANIFEST.md at the root and the DRC reports under reports/.
    Regenerate the MANIFEST and re-anchor the .chiplet layout: ref to layout/;
    update .gitignore, .dockerignore, the adk-new-project scaffold and the READMEs
    in lockstep. Bump the chiplet_kicad_plugin pin to 3603c53.

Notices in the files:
README.md:
License & notices:
This repository is **GPL-3.0-or-later** (`LICENSE`), with one rule on top: a
file's own `SPDX-License-Identifier` line decides its license. The record format
schemas in [`formats/`](formats/) and the files of ours whose SPDX line says
Apache-2.0 (most of `ci/`, `nix/`, `nix-tail/`, their tests and `flake.nix`) are
Apache-2.0**; its text is in
[`formats/LICENSE`](formats/LICENSE). A file with no SPDX line is under `LICENSE`,
and the third-party files `NOTICE.md` lists keep their own license.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
